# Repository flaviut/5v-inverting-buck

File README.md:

# Inverting buck-boost controller

Using the documentation in [TI's SLVA458B, "Creating an Inverting Power Supply Using a Synchronous Step-Down Regulator"][SLVA458B], I've designed an inverting buck-boost regulator using the super-cheap Aerosemi MT2499A, and characterized its performance somewhat.

[SLVA458B]: https://www.ti.com/lit/an/slva458b/slva458b.pdf?ts=1675589999464

[board layers](doc/layers.pdf)

## Testing

There's a massive amount of 7kHz ripple, up to 500mV before stopping testing at 300mA.

This seems to be related to very poor regulator stability. Placing 33pF in C5 improves ripple to 30mV between 0-220mA out, but the ripple is back to 500mV at 230mA.

|Cff |Imax |
|----|-----|
|32pF|225mA|
|54pF|285mA|

Linear interpolation indicates 133pF would be needed for stability at 500mA, but I'm not sure if linear interpolation is valid here.

I also suspect that it is not possible to create a perfectly compensated regulator here, since the MT2499A is internally compensated, and the procedure that SLVA458B describes to compensate the regulator is just not possible.

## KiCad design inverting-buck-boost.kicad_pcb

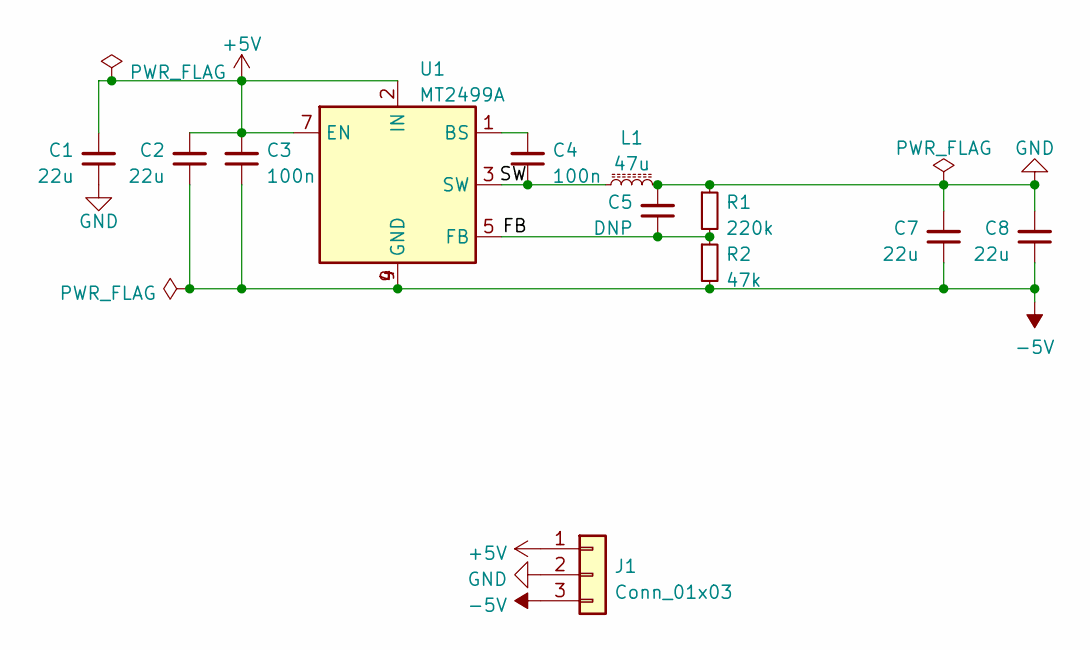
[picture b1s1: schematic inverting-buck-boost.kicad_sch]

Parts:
C1, C2, C7, C8: 22u; C_1210_3225Metric; LCSC C12891
C3, C4: 100n; C_0603_1608Metric; LCSC C14663
C5: DNP; C_0603_1608Metric
J1: Conn_01x03; PinHeader_1x03_P2.54mm_Vertical
L1: 47u; L_Taiyo-Yuden_NR-50xx; LCSC C341038
R1: 220k; R_0603_1608Metric; LCSC C22961
R2: 47k; R_0603_1608Metric; LCSC C25819
U1: MT2499A; SOIC-8-1EP_3.9x4.9mm_P1.27mm_EP2.62x3.51mm_ThermalVias; LCSC C3007555

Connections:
+5V: C1.2, C2.2, C3.2, J1.1, U1.2 (IN), U1.7 (EN)
-5V: C2.1, C3.1, C7.1, C8.1, J1.3, R2.2, U1.4 (GND), U1.9 (GND)
/FB: C5.1, R1.2, R2.1, U1.5 (FB)
/SW: C4.1, L1.2, U1.3 (SW)
GND: C1.1, C5.2, C7.2, C8.2, J1.2, L1.1, R1.1
unnamed: C4.2, U1.1 (BS)

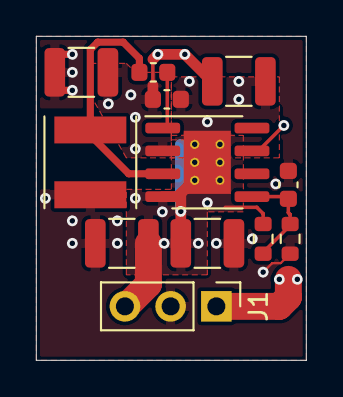
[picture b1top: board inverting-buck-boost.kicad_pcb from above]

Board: 2 copper layers, 15.0 x 18.0 mm, 12 parts (0 on the bottom side), 6 nets.

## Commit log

2023-01-04 Improvements
2023-02-06 Fix resistor to be as designed
2023-02-06 Update 3d models
2023-02-06 Add readme
2023-02-06 Fix table
2023-02-06 Remove inductor fill
    reduces parasitic capacitance
